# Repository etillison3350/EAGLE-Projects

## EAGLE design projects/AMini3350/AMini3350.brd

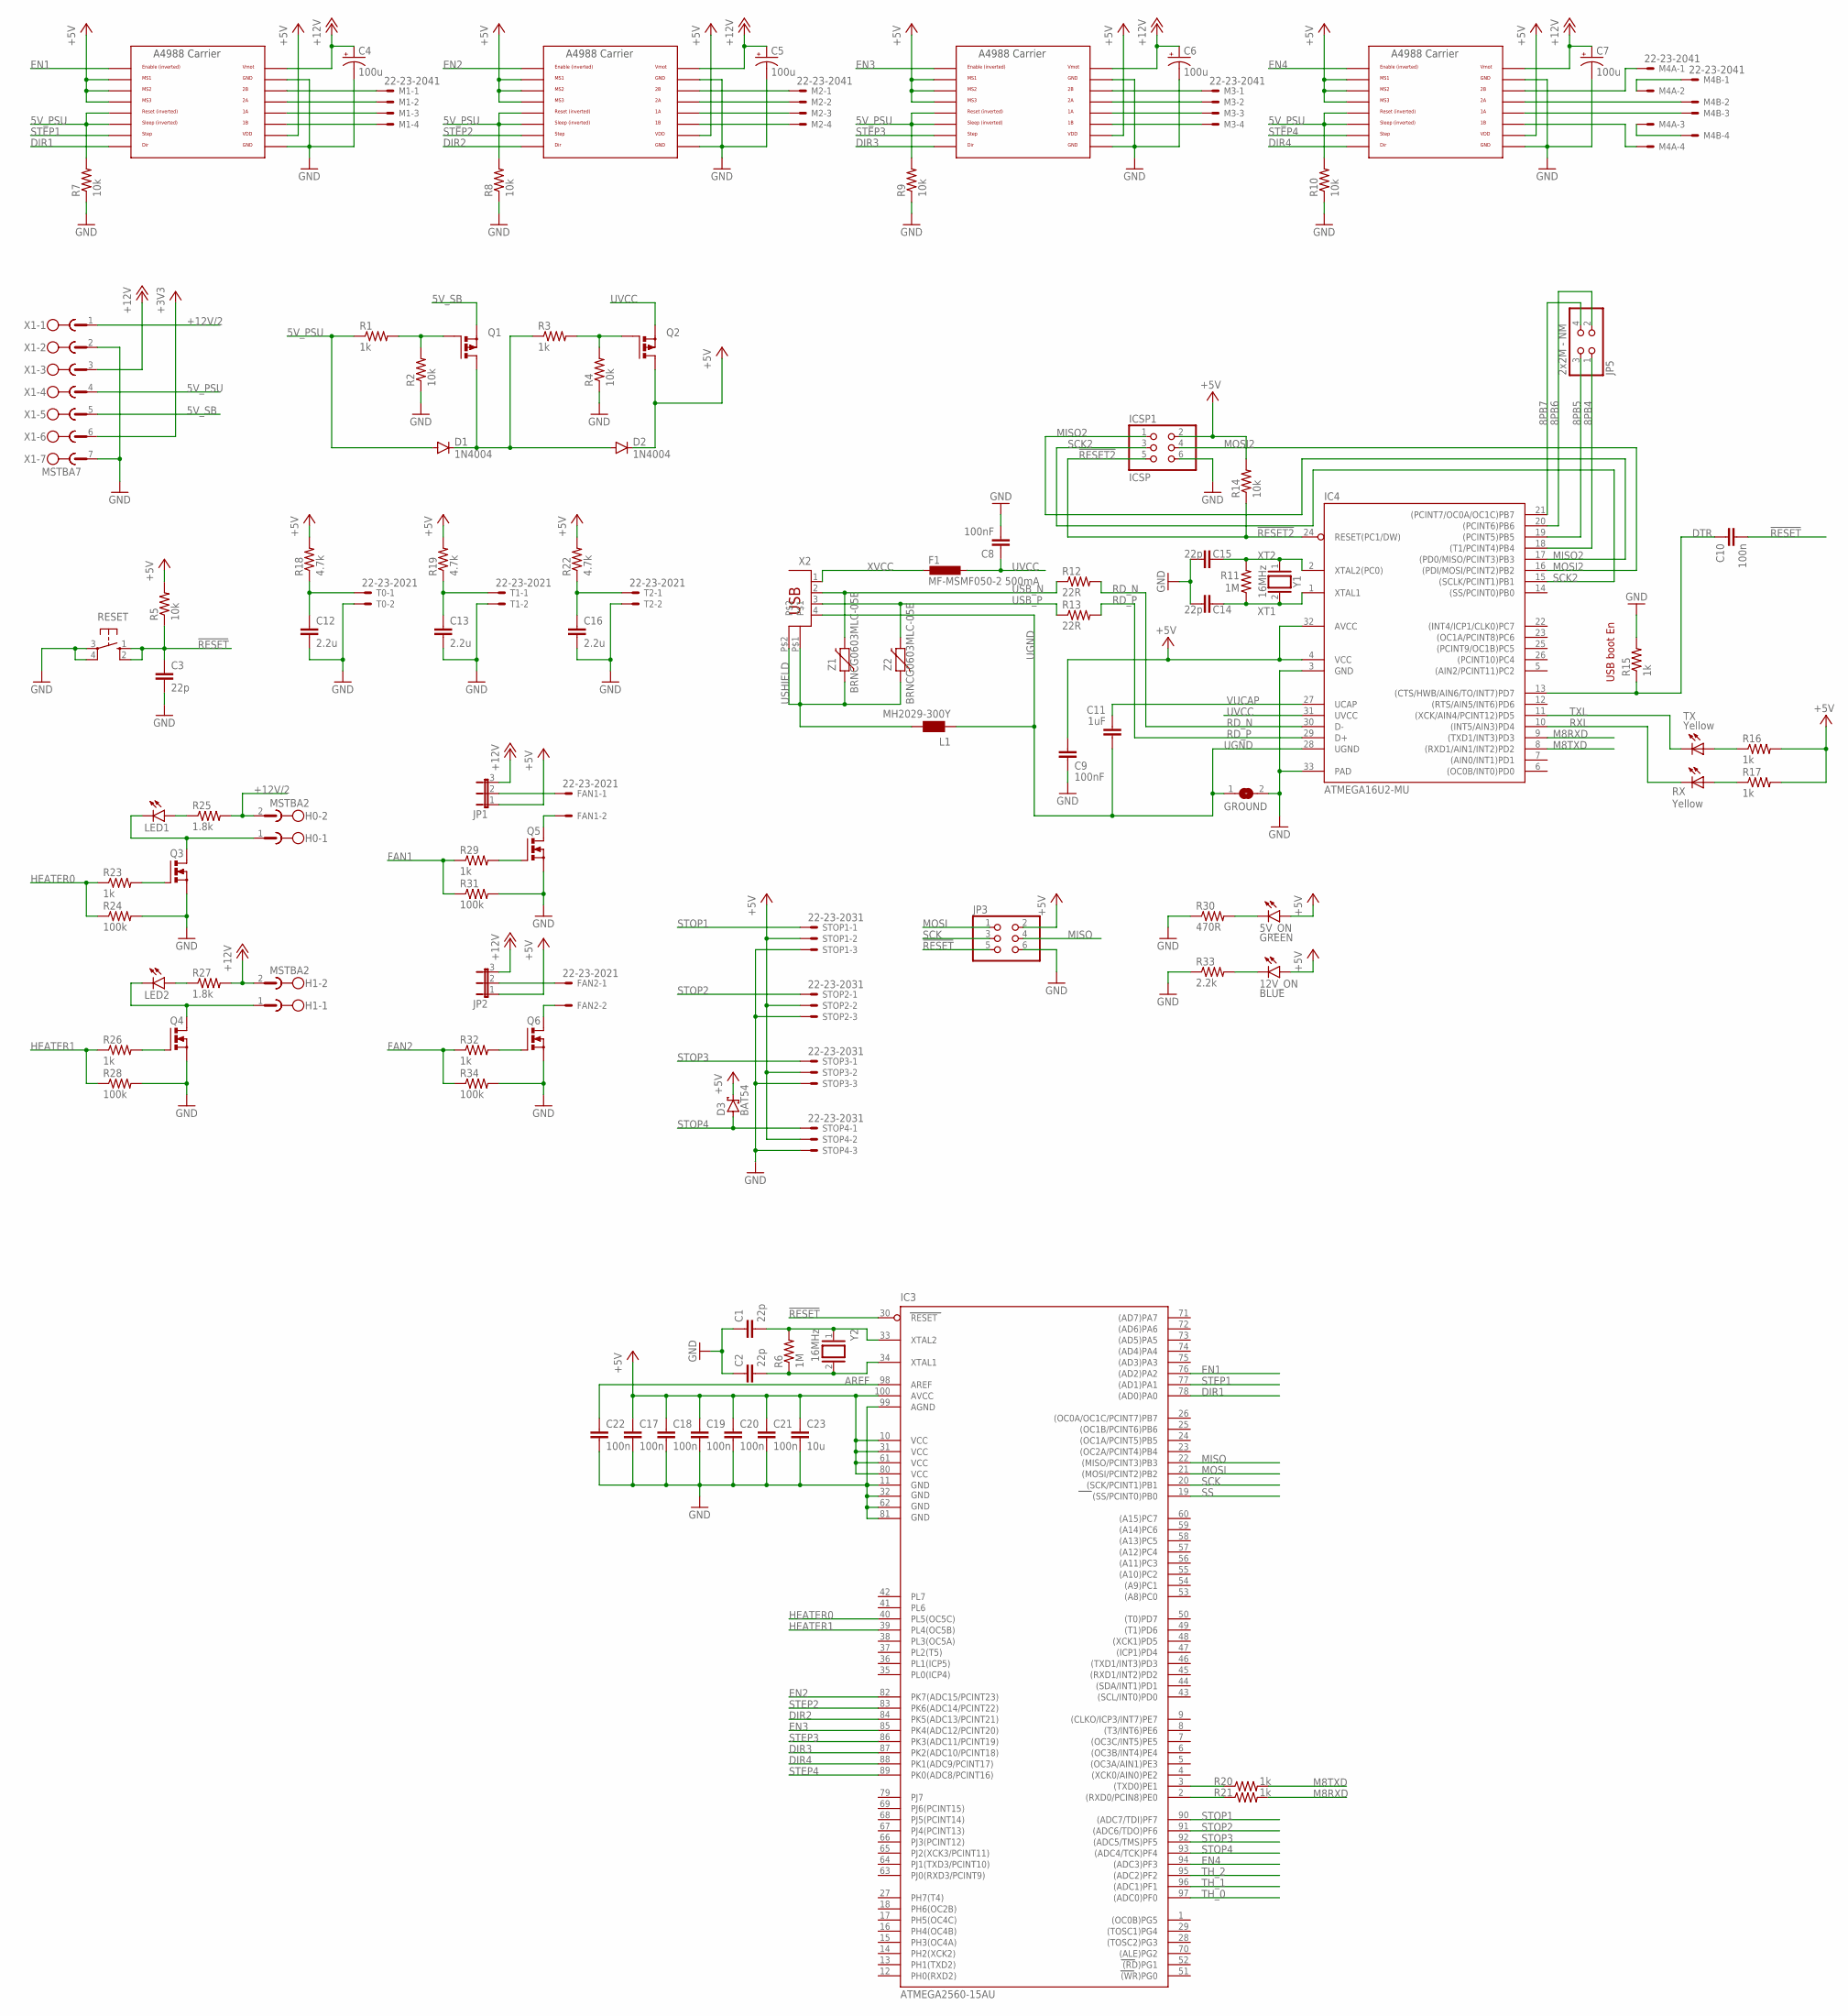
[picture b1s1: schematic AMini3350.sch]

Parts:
5V_ON: GREEN; CHIP-LED0805
12V_ON: BLUE; CHIP-LED0805
C1, C2, C3, C14, C15: 22p; C0603
C4, C5, C6, C7: 100u; PANASONIC_D
C8, C9: 100nF; C0603
C10, C17, C18, C19, C20, C21, C22: 100n; C0603
C11: 1uF; C0603
C12, C13, C16: 2.2u; C0603
C23: 10u; C0805
D1, D2: 1N4004; DO41-10
D3: BAT54; SOT23
F1: MF-MSMF050-2 500mA; L1812
FAN1, FAN2: 22-23-2021
GROUND: SJ
H0, H1: MSTBA2
IC3: ATMEGA2560-15AU; TQFP100
IC4: ATMEGA16U2-MU; MLF32
ICSP1: ICSP; 2X03
JP1, JP2: JP2E; JP2
JP3: PINHD-2X3; 2X03
JP5: 2x2M - NM; 2X02
L1: MH2029-300Y; 0805
LED1, LED2: LEDCHIP-LED0805; CHIP-LED0805
M1, M2, M3, M4A, M4B: 22-23-2041
Q1, Q2: PMOSFET_PTO220BV; TO220BV
Q3, Q4, Q5, Q6: PMOSFET_NTO220BV; TO220BV
R1, R3, R15, R16, R17, R20, R21, R23, R26, R29, R32: 1k; R0603
R2, R4, R5, R7, R8, R9, R10, R14: 10k; R0603
R6, R11: 1M; R0603
R12, R13: 22R; R0603
R18, R19, R22: 4.7k; R0603
R24, R28, R31, R34: 100k; R0603
R25, R27: 1.8k; R0603
R30: 470R; R0603
R33: 2.2k; R0603
RESET: 10-XX; B3F-10XX
RX: Yellow; CHIPLED_0805
STOP1, STOP2, STOP3, STOP4: 22-23-2031
T0, T1, T2: 22-23-2021
TX: Yellow; CHIPLED_0805
U$1, U$2, U$3, U$4: A4988BREAKOUT
X1: MSTBA7
X2: 0056_USB-B-S-RA-WT-SPCC; PN61729
Y1, Y2: 16MHz; QS
Z1, Z2: BRNCG0603MLC-05E; CT/CN0603

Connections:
1A-1: M1.3, U$1.1A
1A-2: M2.3, U$2.1A
1A-3: M3.3, U$3.1A
1A-4: M4B.3, U$4.1A
1B-1: M1.4, U$1.1B
1B-2: M2.4, U$2.1B
1B-3: M3.4, U$3.1B
1B-4: M4A.4, U$4.1B
2A-1: M1.2, U$1.2A
2A-2: M2.2, U$2.2A
2A-3: M3.2, U$3.2A
2A-4: M4B.2, U$4.2A
2B-1: M1.1, U$1.2B
2B-2: M2.1, U$2.2B
2B-3: M3.1, U$3.2B
2B-4: M4A.1, U$4.2B
5V_PSU: D1.A, R1.1, R7.2, R8.2, R9.2, R10.2, U$1.RST, U$1.SLP (SLEEP), U$2.RST, U$2.SLP (SLEEP), U$3.RST, U$3.SLP (SLEEP), U$4.RST, U$4.SLP (SLEEP), X1.4
5V_SB: Q1.S, X1.5
5V_SB_G: Q1.G, R1.2, R2.2
5V_SEL1: D1.C, D2.A, Q1.D, R3.1
8PB4: IC4.18 ((T1/PCINT4)PB4), JP5.1
8PB5: IC4.19 ((PCINT5)PB5), JP5.3
8PB6: IC4.20 ((PCINT6)PB6), JP5.2
8PB7: IC4.21 ((PCINT7/OC0A/OC1C)PB7), JP5.4
!RESET: C3.1, C10.2, IC3.30 (RESET), JP3.5, R5.1, RESET.1 (S), RESET.2 (S1)
!RESET2: IC4.24 (RESET(PC1/DW)), ICSP1.5, R14.1
+3V3: X1.6
+5V: 5V_ON.A, 12V_ON.A, C9.1, C17.1, C18.1, C19.1, C20.1, C21.1, C23.1, D2.C, D3.3 (C), IC3.10 (VCC), IC3.31 (VCC1), IC3.61 (VCC2), IC3.80 (VCC3), IC3.100 (AVCC), IC4.4 (VCC), IC4.32 (AVCC), ICSP1.2, JP1.1, JP2.1, JP3.2, Q2.D, R5.2, R14.2, R16.2, R17.2, R18.2, R19.2, R22.2, STOP1.2, STOP2.2, STOP3.2, STOP4.2, U$1.MS1, U$1.MS2, U$1.MS3, U$1.VDD, U$2.MS1, U$2.MS2, U$2.MS3, U$2.VDD, U$3.MS1, U$3.MS2, U$3.MS3, U$3.VDD, U$4.MS1, U$4.MS2, U$4.MS3, U$4.VDD
+12V: C4.+, C5.+, C6.+, C7.+, H1.2, JP1.3, JP2.3, R27.2, U$1.VMOT, U$2.VMOT, U$3.VMOT, U$4.VMOT, X1.3
+12V/2: H0.2, R25.2, X1.1
AB1-4: M4A.3, M4B.4
AB2-4: M4A.2, M4B.1
AREF: C22.1, IC3.98 (AREF)
DIR1: IC3.78 ((AD0)PA0), U$1.DIR
DIR2: IC3.84 (PK5(ADC13/PCINT21)), U$2.DIR
DIR3: IC3.87 (PK2(ADC10/PCINT18)), U$3.DIR
DIR4: IC3.88 (PK1(ADC9/PCINT17)), U$4.DIR
DTR: C10.1, IC4.13 ((CTS/HWB/AIN6/TO/INT7)PD7), R15.1
EN1: IC3.76 ((AD2)PA2), U$1.EN
EN2: IC3.82 (PK7(ADC15/PCINT23)), U$2.EN
EN3: IC3.85 (PK4(ADC12/PCINT20)), U$3.EN
EN4: IC3.94 ((ADC3)PF3), U$4.EN
FAN1: R29.1, R31.1
FAN1_D: FAN1.2, Q5.D
FAN1_G: Q5.G, R29.2
FAN1_V: FAN1.1, JP1.2
FAN2: R32.1, R34.1
FAN2_D: FAN2.2, Q6.D
FAN2_G: Q6.G, R32.2
FAN2_V: FAN2.1, JP2.2
GND: C1.1, C2.1, C3.2, C4.-, C5.-, C6.-, C7.-, C8.2, C9.2, C12.2, C13.2, C14.2, C15.2, C16.2, C17.2, C18.2, C19.2, C20.2, C21.2, C22.2, C23.2, GROUND.2, IC3.11 (GND), IC3.32 (GND1), IC3.62 (GND2), IC3.81 (GND3), IC3.99 (AGND), IC4.3 (GND), IC4.33 (PAD), ICSP1.6, JP3.6, Q3.S, Q4.S, Q5.S, Q6.S, R2.1, R4.1, R7.1, R8.1, R9.1, R10.1, R15.2, R24.2, R28.2, R30.1, R31.2, R33.1, R34.2, RESET.3, RESET.4 (P1), STOP1.3, STOP2.3, STOP3.3, STOP4.3, T0.2, T1.2, T2.2, U$1.GND, U$1.GND@0 (GND), U$2.GND, U$2.GND@0 (GND), U$3.GND, U$3.GND@0 (GND), U$4.GND, U$4.GND@0 (GND), X1.2, X1.7
H0_D: H0.1, LED1.C, Q3.D
H0_G: Q3.G, R23.2
H0_LED: LED1.A, R25.1
H1_D: H1.1, LED2.C, Q4.D
H1_G: Q4.G, R26.2
H1_LED: LED2.A, R27.1
HEATER0: IC3.40 (PL5(OC5C)), R23.1, R24.1
HEATER1: IC3.39 (PL4(OC5B)), R26.1, R28.1
M8RXD: IC4.9 ((TXD1/INT3)PD3), R21.2
M8TXD: IC4.8 ((RXD1/AIN1/INT2)PD2), R20.2
MISO: IC3.22 ((MISO/PCINT3)PB3), JP3.4
MISO2: IC4.17 ((PD0/MISO/PCINT3)PB3), ICSP1.1
MOSI: IC3.21 ((MOSI/PCINT2)PB2), JP3.1
MOSI2: IC4.16 ((PDI/MOSI/PCINT2)PB2), ICSP1.4
unnamed: 5V_ON.C, R30.2
unnamed: 12V_ON.C, R33.2
RD_N: IC4.30 (D-), R12.2
RD_P: IC4.29 (D+), R13.2
RXD: IC3.2 ((RXD0/PCIN8)PE0), R21.1
RXL: IC4.10 ((INT5/AIN3)PD4), RX.C
RX_L: R17.1, RX.A
SCK: IC3.20 ((SCK/PCINT1)PB1), JP3.3
SCK2: IC4.15 ((SCLK/PCINT1)PB1), ICSP1.3
SS: IC3.19 ((SS/PCINT0)PB0)
STEP1: IC3.77 ((AD1)PA1), U$1.STEP
STEP2: IC3.83 (PK6(ADC14/PCINT22)), U$2.STEP
STEP3: IC3.86 (PK3(ADC11/PCINT19)), U$3.STEP
STEP4: IC3.89 (PK0(ADC8/PCINT16)), U$4.STEP
STOP1: IC3.90 ((ADC7/TDI)PF7), STOP1.1
STOP2: IC3.91 ((ADC6/TDO)PF6), STOP2.1
STOP3: IC3.92 ((ADC5/TMS)PF5), STOP3.1
STOP4: D3.1 (A), IC3.93 ((ADC4/TCK)PF4), STOP4.1
TH_0: C12.1, IC3.97 ((ADC0)PF0), R18.1, T0.1
TH_1: C13.1, IC3.96 ((ADC1)PF1), R19.1, T1.1
TH_2: C16.1, IC3.95 ((ADC2)PF2), R22.1, T2.1
TXD: IC3.3 ((TXD0)PE1), R20.1
TXL: IC4.11 ((XCK/AIN4/PCINT12)PD5), TX.C
TX_L: R16.1, TX.A
UGND: C11.2, GROUND.1, IC4.28 (UGND), L1.1, X2.4
USB_N: R12.1, X2.2, Z1.2
USB_P: R13.1, X2.3, Z2.2
USHIELD: L1.2, X2.P$1, X2.P$2, Z1.1, Z2.1
UVCC: C8.1, F1.1, IC4.31 (UVCC), Q2.S
UVCC_G: Q2.G, R3.2, R4.2
VUCAP: C11.1, IC4.27 (UCAP)
XT1: C14.1, IC4.1 (XTAL1), R11.1, Y1.2
XT2: C15.1, IC4.2 (XTAL2(PC0)), R11.2, Y1.1
XTAL1: C2.2, IC3.34 (XTAL1), R6.1, Y2.2
XTAL2: C1.2, IC3.33 (XTAL2), R6.2, Y2.1
XVCC: F1.2, X2.1

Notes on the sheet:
USB boot En

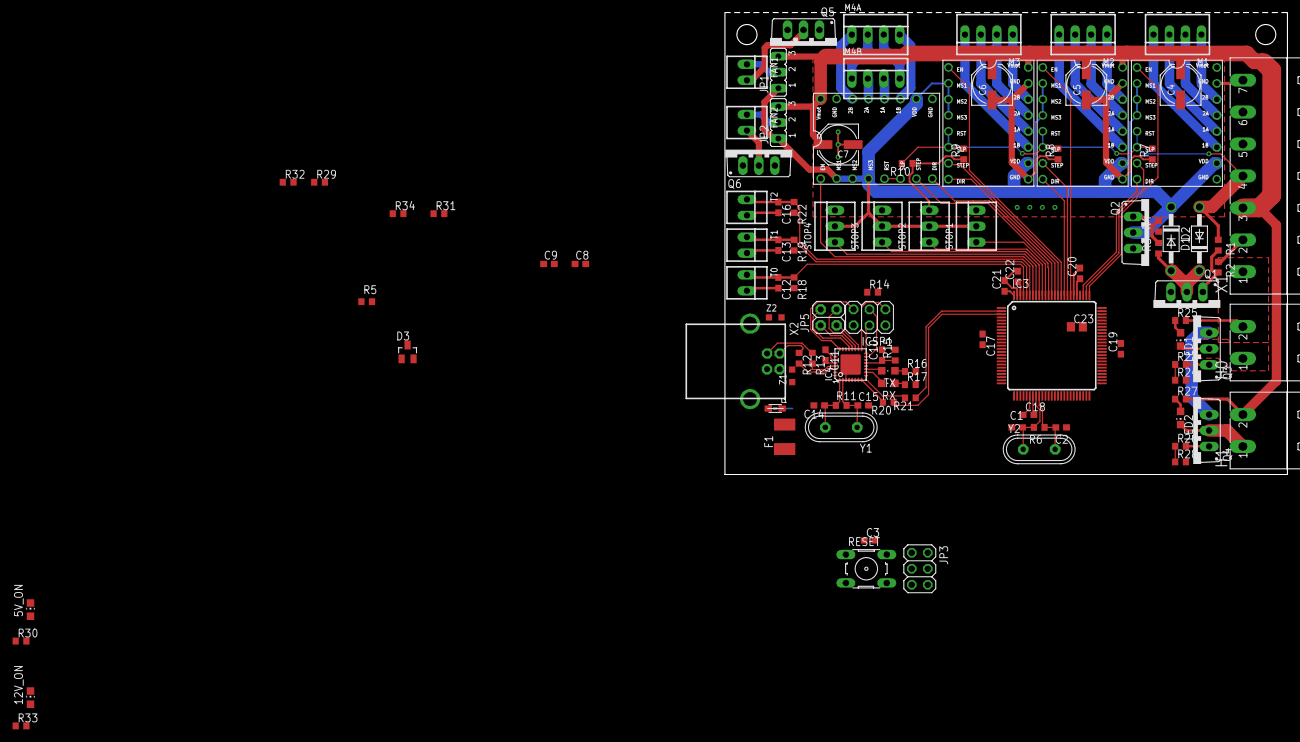
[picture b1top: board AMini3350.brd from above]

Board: 2 copper layers, 89.5 x 73.5 mm, 109 parts (1 on the bottom side), 99 nets.

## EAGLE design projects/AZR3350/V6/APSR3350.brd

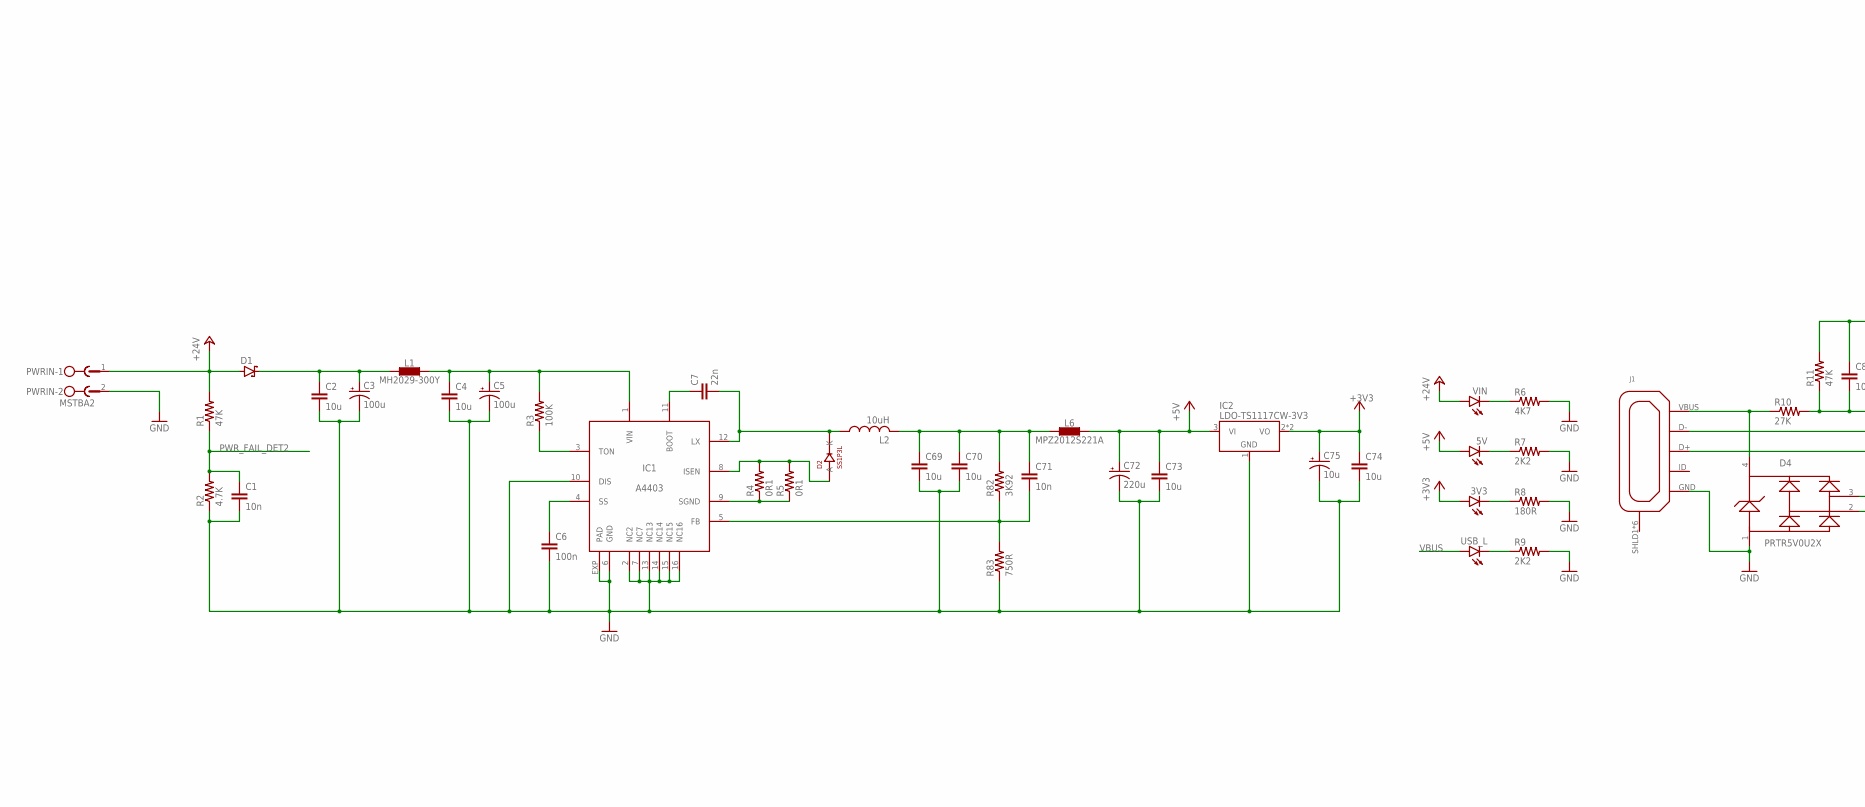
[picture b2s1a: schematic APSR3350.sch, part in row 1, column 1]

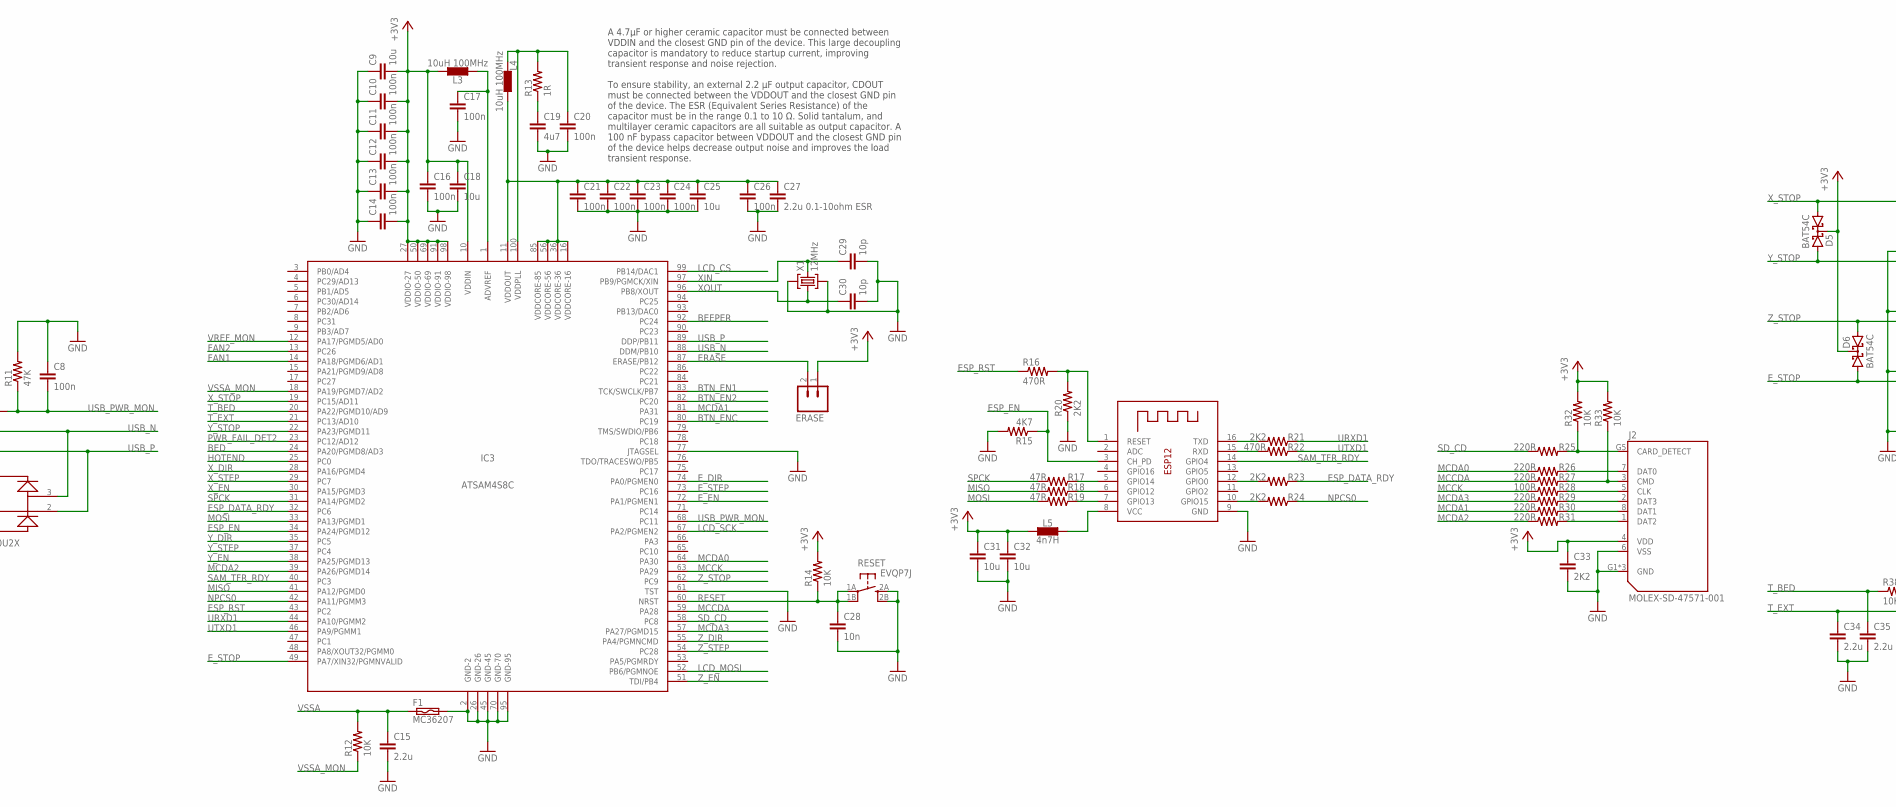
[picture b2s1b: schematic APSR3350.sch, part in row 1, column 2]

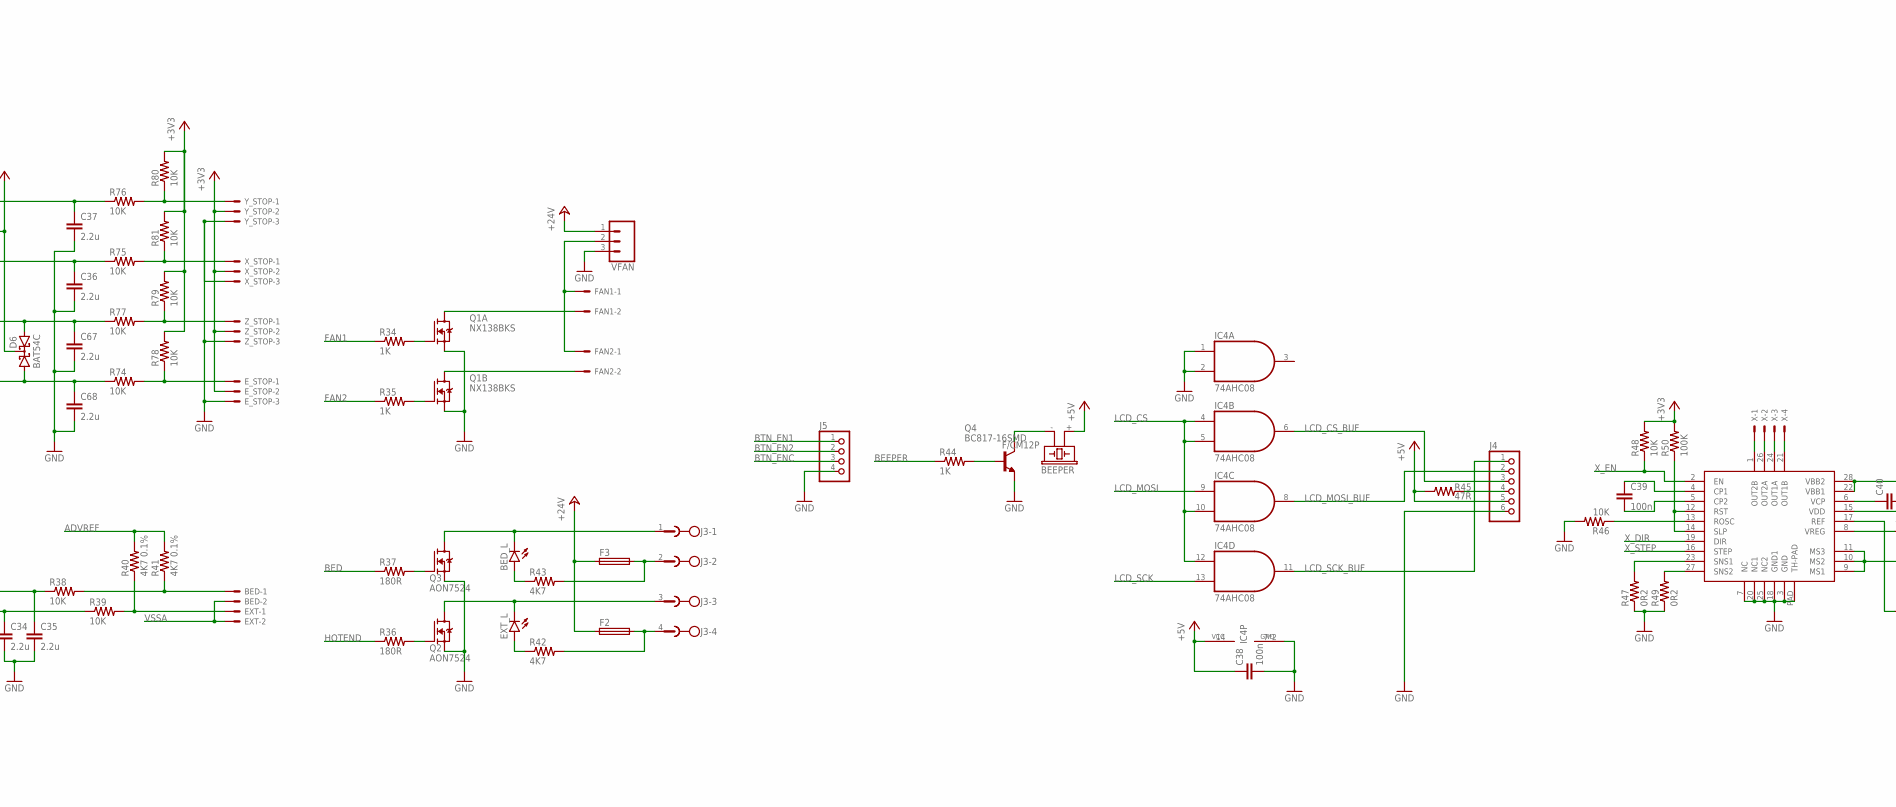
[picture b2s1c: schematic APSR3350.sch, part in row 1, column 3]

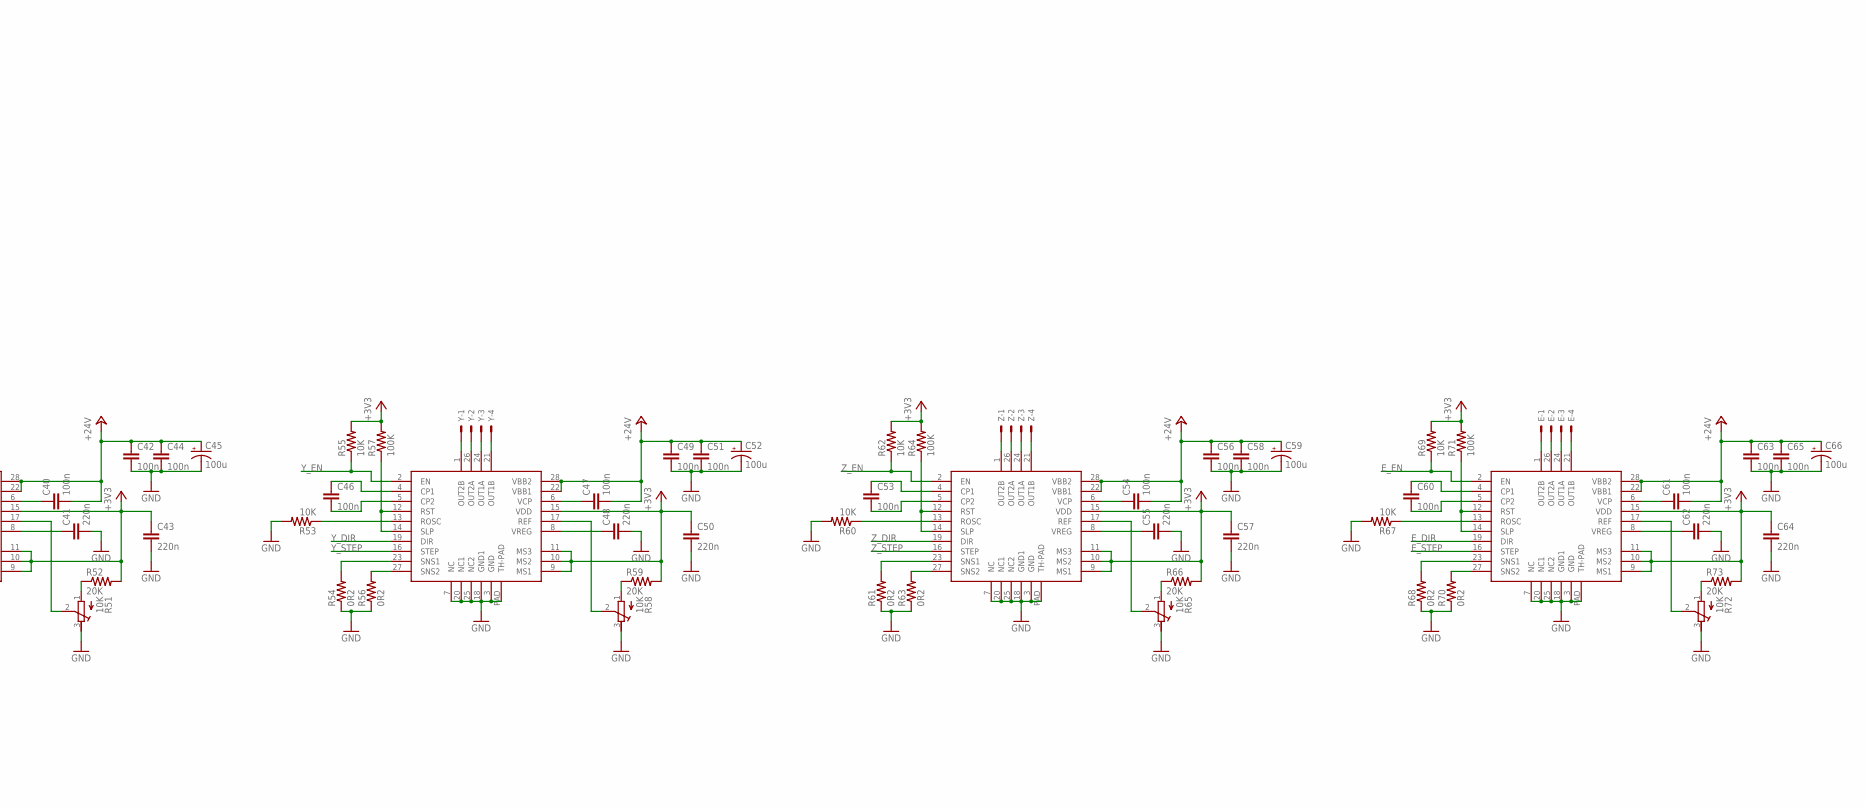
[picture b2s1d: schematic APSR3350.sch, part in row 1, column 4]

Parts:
3V3, 5V: LEDCHIPLED_0805; CHIPLED_0805
BED: KK-254-2; MOLEX-KK-254-2
BED_L: LEDCHIPLED_0805; CHIPLED_0805
BEEPER: F/CM12P
C1, C28, C71: 10n; C0603
C2, C4, C18, C31, C32, C69, C70, C73, C74: 10u; C0603
C3, C5, C45, C52, C59, C66: 100u; PANASONIC_D
C6, C8, C10, C11, C12, C13, C14, C16, C17, C20, C21, C22, C23, C24, C26, C38, C39, C40, C42, C44, C46, C47, C49, C51, C53, C54, C56, C58, C60, C61, C63, C65: 100n; C0603
C7: 22n; C0603
C9, C25: 10u; C0805
C15, C34, C35, C36, C37, C67, C68: 2.2u; C0603
C19: 4u7; C0603
C27: 2.2u 0.1-10ohm ESR; C0603
C29, C30: 10p; C0603
C33: 2K2; C0603
C41, C43, C48, C50, C55, C57, C62, C64: 220n; C0603
C72: 220u; PANASONIC_D
C75: 10u; PANASONIC_D
D1: SCHOTTKY-DIODESMD; SMB
D2: SS1P3L; DO220AAL
D4: PRTR5V0U2XB; SOT143B
D5, D6: BAT54C; SOT23
E: KK-254-4; MOLEX-KK-254-4
ERASE: CONN_02; 1X02
ESP8266: ESP-12
EXT: KK-254-2; MOLEX-KK-254-2
EXT_L: LEDCHIPLED_0805; CHIPLED_0805
E_STOP: KK-254-3; MOLEX-KK-254-3
F1: MC36207
F2, F3: 19560
FAN1, FAN2: KK-254-2; MOLEX-KK-254-2
IC1: A4403; QFN16-4X4
IC2: LDO-TS1117CW-3V3; SOT223
IC3: ATSAM4S8C; LQFP100
IC4: 74AHC08; DHVQFN14
IC7, IC8, IC9, IC10: A4988; QFN28-TP
J1: ZX62-AB-5PA; USB-MICRO-10103594
J2: MOLEX-SD-47571-001; MOLEX-47571
J3: MSTBV4
J4: PINHD-1X6; 1X06
J5: PINHD-1X4; 1X04
L1: MH2029-300Y; C0805
L2: 10uH; SRR0604
L3, L4: 10uH 100MHz; C0603
L5: 4n7H; C0603
L6: MPZ2012S221A; C0805
PWRIN: MSTBA2
Q1: NX138BKS; SOT363_PHILIPS
Q2, Q3: AON7524; 3X3DFN-EP
Q4: BC817-16SMD; SOT23-BEC
R1, R11: 47K; R0603
R2: 4.7K; R0603
R3, R50, R57, R64, R71: 100K; R0603
R4, R5: 0R1; R0603
R6, R15, R42, R43: 4K7; R0603
R7, R9, R20, R21, R23, R24: 2K2; R0603
R8, R36, R37: 180R; R0603
R10: 27K; R0603
R12, R14, R32, R33, R38, R39, R46, R48, R53, R55, R60, R62, R67, R69, R74, R75, R76, R77, R78, R79, R80, R81: 10K; R0603
R13: 1R; R0603
R16, R22: 470R; R0603
R17, R18, R19, R45: 47R; R0603
R25, R26, R27, R29, R30, R31: 220R; R0603
R28: 100R; R0603
R34, R35, R44: 1K; R0603
R40, R41: 4K7 0.1%; R0603
R47, R49, R54, R56, R61, R63, R68, R70: 0R2; R0805
R51, R58, R65, R72: 10K; RTRIM3103
R52, R59, R66, R73: 20K; R0603
R82: 3K92; R0603
R83: 750R; R0603
RESET: EVQP7J; EVQP7
USB_L: LEDCHIPLED_0805; CHIPLED_0805
VFAN: CONN_03SMALL; 1X03_SMALL
VIN: LEDCHIPLED_0805; CHIPLED_0805
X: KK-254-4; MOLEX-KK-254-4
X1: 12MHz; 5.0X3.2_KX-9A
X_STOP: KK-254-3; MOLEX-KK-254-3
Y: KK-254-4; MOLEX-KK-254-4
Y_STOP: KK-254-3; MOLEX-KK-254-3
Z: KK-254-4; MOLEX-KK-254-4
Z_STOP: KK-254-3; MOLEX-KK-254-3

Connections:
3V3_LED: 3V3.C, R8.1
5V_LED: 5V.C, R7.1
24V_LED: R6.1, VIN.C
+3V3: 3V3.A, C9.2, C10.2, C11.2, C12.2, C13.2, C14.2, C16.1, C18.1, C31.1, C32.1, C33.1, C43.1, C50.1, C57.1, C64.1, C74.1, C75.+, D5.3 (CC), D6.3 (CC), ERASE.1, E_STOP.2, IC2.2 (VO), IC2.4 (VO), IC3.10 (VDDIN), IC3.27 (VDDIO-27), IC3.50 (VDDIO-50), IC3.69 (VDDIO-69), IC3.91 (VDDIO-91), IC3.98 (VDDIO-98), IC7.9 (MS1), IC7.10 (MS2), IC7.11 (MS3), IC7.15 (VDD), IC8.9 (MS1), IC8.10 (MS2), IC8.11 (MS3), IC8.15 (VDD), IC9.9 (MS1), IC9.10 (MS2), IC9.11 (MS3), IC9.15 (VDD), IC10.9 (MS1), IC10.10 (MS2), IC10.11 (MS3), IC10.15 (VDD), J2.4 (VDD), L3.2, L5.1, R14.2, R32.2, R33.2, R48.2, R50.2, R52.2, R55.2, R57.2, R59.2, R62.2, R64.2, R66.2, R69.2, R71.2, R73.2, R78.2, R79.2, R80.2, R81.2, X_STOP.2, Y_STOP.2, Z_STOP.2
+5V: 5V.A, BEEPER.+ (1), C38.1, C72.+, C73.1, IC2.3 (VI), IC4.14 (VCC), J4.5, L6.2, R45.1
+24V: C40.2, C42.1, C44.1, C45.+, C47.2, C49.1, C51.1, C52.+, C54.2, C56.1, C58.1, C59.+, C61.2, C63.1, C65.1, C66.+, D1.A, F2.1, F3.1, IC7.22 (VBB1), IC7.28 (VBB2), IC8.22 (VBB1), IC8.28 (VBB2), IC9.22 (VBB1), IC9.28 (VBB2), IC10.22 (VBB1), IC10.28 (VBB2), PWRIN.1, R1.2, VFAN.1, VIN.A
ADVREF: C17.1, IC3.1 (ADVREF), L3.1, R40.2, R41.2
BED: IC3.24 (PA20/PGMD8/AD3), R37.1
BED_D: BED_L.C, J3.1, Q3.5 (D), Q3.6 (D), Q3.7 (D), Q3.8 (D), Q3.E1 (D), Q3.E2 (D), Q3.PAD (D)
BED_FUSED: F3.2, J3.2, R43.2
BED_G: Q3.4 (G), R37.2
BED_L: BED_L.A, R43.1
BEEPER: IC3.92 (PC24), R44.1
BEEP_G: Q4.B, R44.2
BEEP_OUT: BEEPER.- (2), Q4.C
BOOT: C7.1, IC1.11 (BOOT)
BTN_EN1: IC3.83 (TCK/SWCLK/PB7), J5.1
BTN_EN2: IC3.82 (PC20), J5.2
BTN_ENC: IC3.80 (PC19), J5.3
CLK: J2.5 (CLK), R28.2
CMD: J2.3 (CMD), R27.2, R33.1
CON: J4.4, R45.2
CP1E: C60.1, IC10.4 (CP1)
CP1X: C39.1, IC7.4 (CP1)
CP1Y: C46.1, IC8.4 (CP1)
CP1Z: C53.1, IC9.4 (CP1)
CP2E: C60.2, IC10.5 (CP2)
CP2X: C39.2, IC7.5 (CP2)
CP2Y: C46.2, IC8.5 (CP2)
CP2Z: C53.2, IC9.5 (CP2)
DAT0: J2.7 (DAT0), R26.2
DAT1: J2.8 (DAT1), R30.2
DAT2: J2.1 (DAT2), R31.2
DAT3: J2.2 (DAT3), R29.2
DET: J2.G5 (CARD_DETECT), R25.2, R32.1
EDR_CONN: ESP8266.12 (GPIO0), R23.2
EMOT1A: E.3, IC10.24 (OUT1A)
EMOT1B: E.4, IC10.21 (OUT1B)
EMOT2A: E.2, IC10.26 (OUT2A)
EMOT2B: E.1, IC10.1 (OUT2B)
ERASE: ERASE.2, IC3.87 (ERASE/PB12)
ESP_CS: ESP8266.10 (GPIO15), R24.2
ESP_DATA_RDY: IC3.32 (PC6), R23.1
ESP_EN: ESP8266.3 (CH_PD), IC3.34 (PA24/PGMD12), R15.1
ESP_MISO: ESP8266.6 (GPIO12), R18.1
ESP_MOSI: ESP8266.7 (GPIO13), R19.1
ESP_RESET: ESP8266.1 (RESET), R16.2, R20.2
ESP_RST: IC3.43 (PC2), R16.1
ESP_SPCK: ESP8266.5 (GPIO14), R17.1
ESP_URDX: ESP8266.16 (TXD), R21.2
ESP_UTDX: ESP8266.15 (RXD), R22.2
ESP_VIN: ESP8266.8 (VCC), L5.2
EXT_D: EXT_L.C, J3.3, Q2.5 (D), Q2.6 (D), Q2.7 (D), Q2.8 (D), Q2.E1 (D), Q2.E2 (D), Q2.PAD (D)
EXT_FUSED: F2.2, J3.4, R42.2
EXT_G: Q2.4 (G), R36.2
EXT_L: EXT_L.A, R42.1
E_DIR: IC3.74 (PA0/PGMEN0), IC10.19 (DIR)
E_EN: IC3.72 (PA1/PGMEN1), IC10.2 (EN), R69.1
E_STEP: IC3.73 (PC16), IC10.16 (STEP)
E_STOP: C68.1, D6.1 (A1), IC3.49 (PA7/XIN32/PGMNVALID), R74.1
E_STOP_IN: E_STOP.1, R74.2, R78.1
FAN1: IC3.14 (PA18/PGMD6/AD1), R34.1
FAN1_D: FAN1.2, Q1.6 (D)
FAN1_G: Q1.2 (G), R34.2
FAN2: IC3.13 (PC26), R35.1
FAN2_D: FAN2.2, Q1.3 (D)
FAN2_G: Q1.5 (G), R35.2
FB: C71.2, IC1.5 (FB), R82.1, R83.2
GND: C1.2, C2.2, C3.-, C4.2, C5.-, C6.2, C8.1, C9.1, C10.1, C11.1, C12.1, C13.1, C14.1, C15.2, C16.2, C17.2, C18.2, C19.2, C20.2, C21.2, C22.2, C23.2, C24.2, C25.2, C26.2, C27.2, C28.2, C29.2, C30.2, C31.2, C32.2, C33.2, C34.2, C35.2, C36.2, C37.2, C38.2, C41.2, C42.2, C43.2, C44.2, C45.-, C48.2, C49.2, C50.2, C51.2, C52.-, C55.2, C56.2, C57.2, C58.2, C59.-, C62.2, C63.2, C64.2, C65.2, C66.-, C67.2, C68.2, C69.2, C70.2, C72.-, C73.2, C74.2, C75.-, D4.1, ESP8266.9 (GND), E_STOP.3, F1.2, IC1.2 (NC2), IC1.6 (GND), IC1.7 (NC7), IC1.10 (DIS), IC1.13 (NC13), IC1.14 (NC14), IC1.15 (NC15), IC1.16 (NC16), IC1.EXP (PAD), IC2.1 (GND), IC3.2 (GND-2), IC3.26 (GND-26), IC3.45 (GND-45), IC3.61 (TST), IC3.70 (GND-70), IC3.77 (JTAGSEL), IC3.95 (GND-95), IC4.1 (I0), IC4.2 (I1), IC4.7 (GND), IC4.EXP (GND), IC7.3 (GND), IC7.7 (NC), IC7.18 (GND1), IC7.20 (NC1), IC7.25 (NC2), IC7.PAD (TH-PAD), IC8.3 (GND), IC8.7 (NC), IC8.18 (GND1), IC8.20 (NC1), IC8.25 (NC2), IC8.PAD (TH-PAD), IC9.3 (GND), IC9.7 (NC), IC9.18 (GND1), IC9.20 (NC1), IC9.25 (NC2), IC9.PAD (TH-PAD), IC10.3 (GND), IC10.7 (NC), IC10.18 (GND1), IC10.20 (NC1), IC10.25 (NC2), IC10.PAD (TH-PAD), J1.GND, J2.6 (VSS), J2.G1 (GND), J2.G2 (GND), J2.G3 (GND), J4.6, J5.4, PWRIN.2, Q1.1 (S), Q1.4 (S), Q2.1 (S), Q2.2 (S), Q2.3 (S), Q3.1 (S), Q3.2 (S), Q3.3 (S), Q4.E, R2.1, R6.2, R7.2, R8.2, R9.2, R11.2, R15.2, R20.1, R46.2, R47.1, R49.1, R51.3 (E), R53.2, R54.1, R56.1, R58.3 (E)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
HOTEND: IC3.25 (PC0), R36.1
IDEK: C19.1, R13.1
ISEN: D2.P$2 (A), IC1.8 (ISEN), R4.2, R5.2
LCD_CS: IC3.99 (PB14/DAC1), IC4.4 (I0), IC4.5 (I1), IC4.10 (I1), IC4.12 (I0)
LCD_CS_BUF: IC4.6 (O), J4.3
LCD_MOSI: IC3.52 (PB6/PGMNOE), IC4.9 (I0)
LCD_MOSI_BUF: IC4.8 (O), J4.2
LCD_SCK: IC3.67 (PA2/PGMEN2), IC4.13 (I1)
LCD_SCK_BUF: IC4.11 (O), J4.1
LX: C7.2, D2.P$1 (K), IC1.12 (LX), L2.P$1 (1)
MCCDA: IC3.59 (PA28), R27.1
MCCK: IC3.63 (PA29), R28.1
MCDA0: IC3.64 (PA30), R26.1
MCDA1: IC3.81 (PA31), R30.1
MCDA2: IC3.39 (PA26/PGMD14), R31.1
MCDA3: IC3.57 (PA27/PGMD15), R29.1
MISO: IC3.41 (PA12/PGMD0), R18.2
MOSI: IC3.33 (PA13/PGMD1), R19.2
NPCS0: IC3.42 (PA11/PGMM3), R24.1
PWR_FAIL_DET2: C1.1, IC3.23 (PC12/AD12), R1.1, R2.2
REFE: IC10.17 (REF), R72.2 (S)
REFE-IN: R72.1 (A), R73.1
REFX: IC7.17 (REF), R51.2 (S)
REFX-IN: R51.1 (A), R52.1
REFY: IC8.17 (REF), R58.2 (S)
REFY-IN: R58.1 (A), R59.1
REFZ: IC9.17 (REF), R65.2 (S)
REFZ-IN: R65.1 (A), R66.1
RESET: C28.1, IC3.60 (NRST), R14.1, RESET.1A, RESET.1B (P1)
ROSCE: IC10.13 (ROSC), R67.1
ROSCX: IC7.13 (ROSC), R46.1
ROSCY: IC8.13 (ROSC), R53.1
ROSCZ: IC9.13 (ROSC), R60.1
RSTE: IC10.12 (RST), IC10.14 (SLP), R71.1
RSTX: IC7.12 (RST), IC7.14 (SLP), R50.1
RSTY: IC8.12 (RST), IC8.14 (SLP), R57.1
RSTZ: IC9.12 (RST), IC9.14 (SLP), R64.1
SAM_TFR_RDY: ESP8266.14 (GPIO4), IC3.40 (PC3)
SD_CD: IC3.58 (PC8), R25.1
SGND: IC1.9 (SGND), R4.1, R5.1
SNS1E: IC10.23 (SNS1), R68.2
SNS1X: IC7.23 (SNS1), R47.2
SNS1Y: IC8.23 (SNS1), R54.2
SNS1Z: IC9.23 (SNS1), R61.2
SNS2E: IC10.27 (SNS2), R70.2
SNS2X: IC7.27 (SNS2), R49.2
SNS2Y: IC8.27 (SNS2), R56.2
SNS2Z: IC9.27 (SNS2), R63.2
SPCK: IC3.31 (PA14/PGMD2), R17.2
SS: C6.1, IC1.4 (SS)
TON: IC1.3 (TON), R3.1
T_BED: C35.1, IC3.20 (PA22/PGMD10/AD9), R38.1
T_BED_IN: BED.1, R38.2, R41.1
T_EXT: C34.1, IC3.21 (PC13/AD10), R39.1
T_EXT_IN: EXT.1, R39.2, R40.1
URXD1: IC3.44 (PA10/PGMM2), R21.1
USB_LED: R9.1, USB_L.C
USB_N: D4.3, IC3.88 (DDM/PB10), J1.D-
USB_P: D4.2, IC3.89 (DDP/PB11), J1.D+
USB_PWR_MON: C8.2, IC3.68 (PC11), R10.2, R11.1
UTXD1: IC3.46 (PA9/PGMM1), R22.1
VBUS: D4.4, J1.VBUS (VUSB), R10.1, USB_L.A
VCPE: C61.1, IC10.6 (VCP)
VCPX: C40.1, IC7.6 (VCP)
VCPY: C47.1, IC8.6 (VCP)
VCPZ: C54.1, IC9.6 (VCP)
VDDOUT: C21.1, C22.1, C23.1, C24.1, C25.1, C26.1, C27.1, IC3.11 (VDDOUT), IC3.16 (VDDCORE-16), IC3.36 (VDDCORE-36), IC3.56 (VDDCORE-56), IC3.85 (VDDCORE-85), L4.2
VDDPLL: C20.1, IC3.100 (VDDPLL), L4.1, R13.2
VIN: C2.1, C3.+, D1.C, L1.1
VIN_F: C4.1, C5.+, IC1.1 (VIN), L1.2, R3.2
VOUT: C69.1, C70.1, C71.1, L2.P$2 (2), L6.1, R82.2
VREF_MON: IC3.12 (PA17/PGMD5/AD0)
VREGE: C62.1, IC10.8 (VREG)
VREGX: C41.1, IC7.8 (VREG)
VREGY: C48.1, IC8.8 (VREG)
VREGZ: C55.1, IC9.8 (VREG)
VSSA: BED.2, C15.1, EXT.2, F1.1, R12.2
VSSA_MON: IC3.18 (PA19/PGMD7/AD2), R12.1
V_FAN: FAN1.1, FAN2.1, VFAN.2
XIN: C29.1, IC3.97 (PB9/PGMCK/XIN), X1.3
XMOT1A: IC7.24 (OUT1A), X.3
XMOT1B: IC7.21 (OUT1B), X.4
XMOT2A: IC7.26 (OUT2A), X.2
XMOT2B: IC7.1 (OUT2B), X.1
XOUT: C30.1, IC3.96 (PB8/XOUT), X1.1
X_DIR: IC3.28 (PA16/PGMD4), IC7.19 (DIR)
X_EN: IC3.30 (PA15/PGMD3), IC7.2 (EN), R48.1
X_STEP: IC3.29 (PC7), IC7.16 (STEP)
X_STOP: C37.1, D5.1 (A1), IC3.19 (PC15/AD11), R76.1
X_STOP_IN: R76.2, R80.1, Y_STOP.1
YMOT1A: IC8.24 (OUT1A), Y.3
YMOT1B: IC8.21 (OUT1B), Y.4
YMOT2A: IC8.26 (OUT2A), Y.2
YMOT2B: IC8.1 (OUT2B), Y.1
Y_DIR: IC3.35 (PC5), IC8.19 (DIR)
Y_EN: IC3.38 (PA25/PGMD13), IC8.2 (EN), R55.1
Y_STEP: IC3.37 (PC4), IC8.16 (STEP)
Y_STOP: C36.1, D5.2 (A2), IC3.22 (PA23/PGMD11), R75.1
Y_STOP_IN: R75.2, R81.1, X_STOP.1
ZMOT1A: IC9.24 (OUT1A), Z.3
ZMOT1B: IC9.21 (OUT1B), Z.4
ZMOT2A: IC9.26 (OUT2A), Z.2
ZMOT2B: IC9.1 (OUT2B), Z.1
Z_DIR: IC3.55 (PA4/PGMNCMD), IC9.19 (DIR)
Z_EN: IC3.51 (TDI/PB4), IC9.2 (EN), R62.1
Z_STEP: IC3.54 (PC28), IC9.16 (STEP)
Z_STOP: C67.1, D6.2 (A2), IC3.62 (PC9), R77.1
Z_STOP_IN: R77.2, R79.1, Z_STOP.1

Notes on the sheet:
A 4.7µF or higher ceramic capacitor must be connected between VDDIN and the closest GND pin of the device. This large decoupling capacitor is mandatory to reduce startup current, improving transient response and noise rejection. To ensure stability, an external 2.2 µF output capacitor, CDOUT must b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

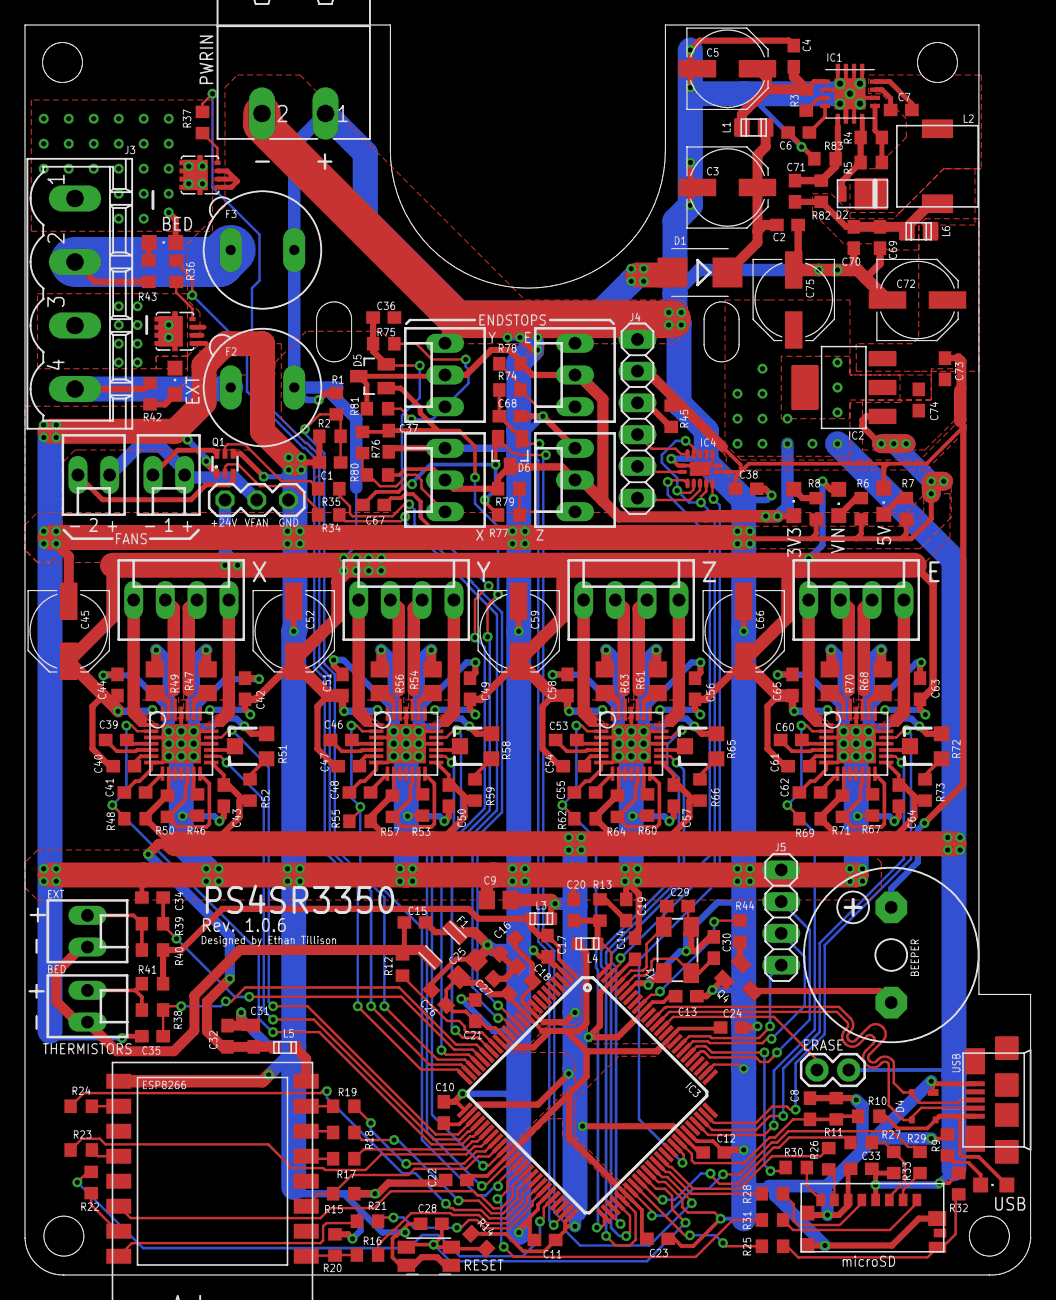
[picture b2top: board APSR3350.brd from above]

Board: 2 copper layers, 80.5 x 100.0 mm, 214 parts (0 on the bottom side), 176 nets.

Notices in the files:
parts and their libraries:
SparkFun-Connectors: Licensing: Creative Commons ShareAlike 4.0 International - https://creativecommons.org/licenses/by-sa/4.0
